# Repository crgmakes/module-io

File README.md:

# I/O Module

All the source files for the I/O module hardware.

# Software 

You will need [KiCad](https://kicad.org) to view and edit this design. Click [here](https://www.kicad.org/download/) to download.

You will also need all the associated libraries and models to drive the design if you want to make changes or view the 3D rendering:

https://github.com/crgmakes/kicad-library.git

Kicad MUST be configured properly to use all the files in this repo. Once you have Kicad installed, under Preferences->Configure Paths..., make the following entries:

1. KICAD_USER_DIR -> set to the root location of where you placed the above repository.
2. KICAD_USER_LIBRARY = ${KICAD_USER_DIR}/Library
3. KICAD_USER_MODEL_DIR = ${KICAD_USER_LIBRARY}/models
4. KICAD_USER_TEMPLATE_DIR = ${KICAD_USER_LIBRARY}/templates	

Kicad will operate mostly normally if these are not set properly. You will notice an issue when you view the PCB in 3D mode.

***NOTE***: after makeing a release build in git, if your rendered 3D images are missing components, ensure the path to EVERY component model is set to ${KICAD_USER_MODEL_DIR}/<model name>.

Kicad sometimes replaces the variable with an expansion and that FAILS during the build process because the expanded variable is local and does not match the build environment.

---

THE DESIGN IS PROVIDED "AS IS" AND THE AUTHOR DISCLAIMS ALL WARRANTIES WITH REGARD TO THIS DESIGN INCLUDING ALL IMPLIED WARRANTIES OF MERCHANTABILITY AND FITNESS. IN NO EVENT SHALL THE AUTHOR BE LIABLE FOR ANY SPECIAL, DIRECT, INDIRECT, OR CONSEQUENTIAL DAMAGES OR ANY DAMAGES WHATSOEVER RESULTING FROM LOSS OF USE, DATA OR PROFITS, WHETHER IN AN ACTION OF CONTRACT, NEGLIGENCE OR OTHER TORTIOUS ACTION, ARISING OUT OF OR IN CONNECTION WITH THE USE OR PERFORMANCE OF THIS DESIGN.

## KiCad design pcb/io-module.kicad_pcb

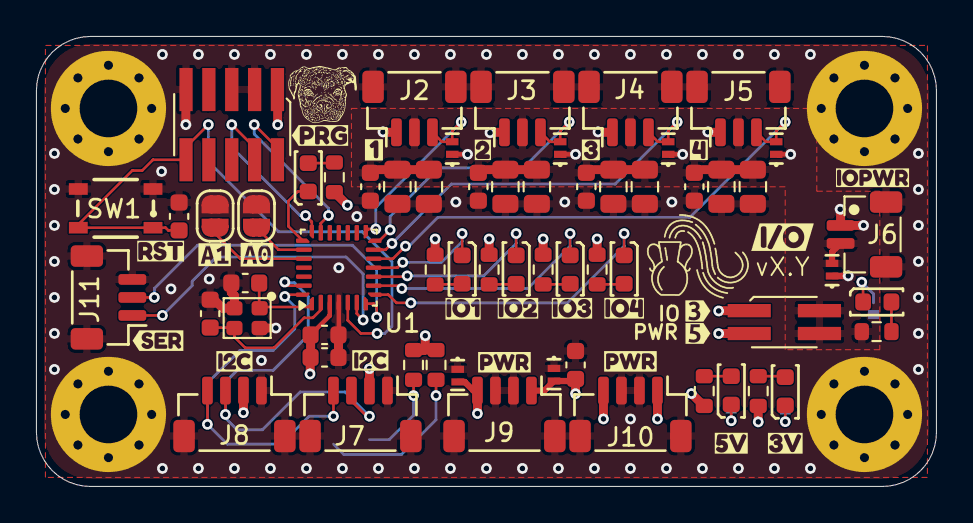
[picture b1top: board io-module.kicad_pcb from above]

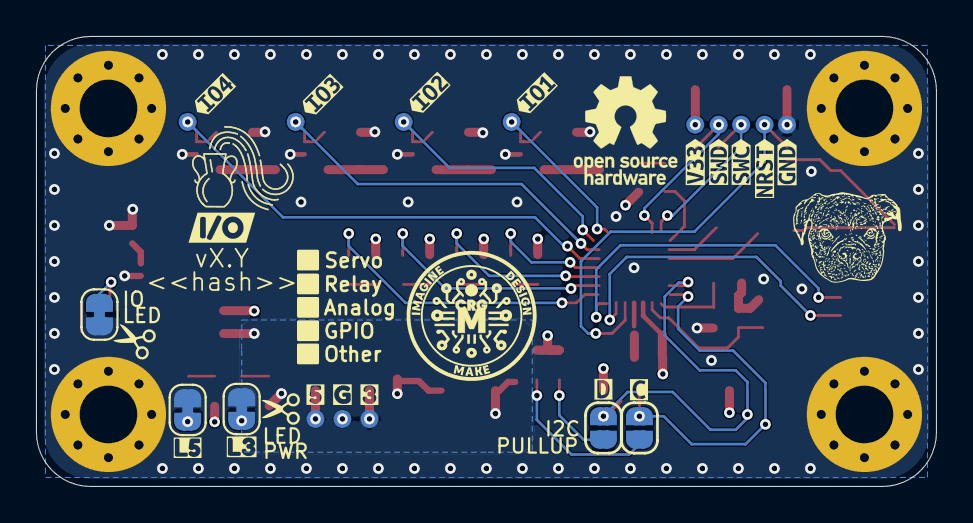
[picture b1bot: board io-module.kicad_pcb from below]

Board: 4 copper layers, 50.0 x 25.0 mm, 127 parts (38 on the bottom side), 37 nets.

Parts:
C1, C2: 4.7pF; C_0603_1608Metric
C3: 4.7uF; C_0603_1608Metric
C4, C5, C9, C12, C15, C18: 0.1uF; C_0603_1608Metric
C7, C8, C10, C11, C13, C14, C16, C17: 47uF; C_0805_2012Metric
C19: 10uF; C_0603_1608Metric
D1, D2, D3, D4, D12, D13, D14, D15: Blue; LED_0603_1608Metric
D5, D10: PESD5V5C1BL; DFN1006-2
D6, D7, D8, D9, D11: PESD3V3S1BL; DFN1006-2
H1, H2, H3, H4: MountingHole; MountingHole_3.2mm_M3_Pad_Via
J1: SWD Header; PinHeader_2x05_P1.27mm_Vertical_SMD
J2, J3, J4, J5, J11: JST_SH_BM03B-SRSS-TB_1x03-1MP_P1.00mm_Vertical
J6: JST_SH_BM02B-SRSS-TB_1x02-1MP_P1.00mm_Vertical
J7, J8, J9, J10: JST_SH_BM04B-SRSS-TB_1x04-1MP_P1.00mm_Vertical
J12: Conn_02x02_Odd_Even; PinHeader_2x02_P1.27mm_Vertical_SMD
JP1, JP2, JP3, JP4: SolderJumper_2_Open; SolderJumper-2_P1.3mm_Open_RoundedPad1.0x1.5mm
JP6, JP7, JP8: SolderJumper_2_Bridged; SolderJumper-2_P1.3mm_Bridged_RoundedPad1.0x1.5mm
LOGO1, LOGO2: Aquarius Logo 5mm
LOGO3: CRGM Logo 7mm
LOGO4: Logo_Open_Hardware_Small; OSHW-Logo_5.7x6mm_SilkScreen
LOGO5: Roxy 3.5mm
LOGO6: Roxy 6.5mm
R1, R2, R7, R9: 4.7K; R_0603_1608Metric
R3, R4, R5, R6, R8, R10: 1K; R_0603_1608Metric
SW1: SKRPABE010; SMD-4P-4.2x3.2mm
TP1, TP2, TP3, TP9, TP10, TP17, TP18, TP19: TestPoint_Pad_D1.0mm
TP11: SERVO1; TestPoint_Pad_D1.0mm
TP12: SERVO2; TestPoint_Pad_D1.0mm
TP13: SERVO3; TestPoint_Pad_D1.0mm
TP14: SERVO4; TestPoint_Pad_D1.0mm
U1: STM32C051G8Ux; QFN-28_4x4mm_P0.5mm
Y1: ECS-480-10-37B2-RWN-TR; Crystal_SMD_2016-4Pin_2.0x1.6mm
kibuzzard-6A2A39A2: G***; kibuzzard-6A2A39A2
kibuzzard-6A2A39A9: G***; kibuzzard-6A2A39A9
kibuzzard-6A2A39B0: G***; kibuzzard-6A2A39B0
kibuzzard-6A2B43CF: G***; kibuzzard-6A2B43CF
kibuzzard-6A2D8D87: G***; kibuzzard-6A2D8D87
kibuzzard-6A2EE621: G***; kibuzzard-6A2EE621
kibuzzard-6A2EE631: G***; kibuzzard-6A2EE631
kibuzzard-6A540D5A: G***; kibuzzard-6A540D5A
kibuzzard-6A540D7E: G***; kibuzzard-6A540D7E
kibuzzard-6A540D73: G***; kibuzzard-6A540D73
kibuzzard-6A540D79: G***; kibuzzard-6A540D79
kibuzzard-6A540D85: G***; kibuzzard-6A540D85
kibuzzard-6A972EAD: G***; kibuzzard-6A972EAD
kibuzzard-6A972EB4: G***; kibuzzard-6A972EB4
kibuzzard-6A7271F3: G***; kibuzzard-6A7271F3
kibuzzard-6A72720D: G***; kibuzzard-6A72720D
kibuzzard-6A72721E: G***; kibuzzard-6A72721E
kibuzzard-6A72852B: G***; kibuzzard-6A72852B
kibuzzard-6A72853D: G***; kibuzzard-6A72853D
kibuzzard-6A98747D: G***; kibuzzard-6A98747D
kibuzzard-6A727216: G***; kibuzzard-6A727216
kibuzzard-6A727224: G***; kibuzzard-6A727224
kibuzzard-6A727235: G***; kibuzzard-6A727235
kibuzzard-6A727258: G***; kibuzzard-6A727258
kibuzzard-6A728531: G***; kibuzzard-6A728531
kibuzzard-6A728536: G***; kibuzzard-6A728536
kibuzzard-690A7DF7: G***; kibuzzard-690A7DF7
kibuzzard-690A7E03: G***; kibuzzard-690A7E03
kibuzzard-690AC3C6: G***; kibuzzard-690AC3C6
kibuzzard-690AC3CC: G***; kibuzzard-690AC3CC
kibuzzard-690AC3D2: G***; kibuzzard-690AC3D2
kibuzzard-690D5FD9: G***; kibuzzard-690D5FD9
kibuzzard-690D5FF2: G***; kibuzzard-690D5FF2
kibuzzard-6954A310: G***; kibuzzard-6954A310
kibuzzard-6954A315: G***; kibuzzard-6954A315
kibuzzard-691760A0: G***; kibuzzard-691760A0
kibuzzard-6917603D: G***; kibuzzard-6917603D
kibuzzard-6917608E: G***; kibuzzard-6917608E
kibuzzard-69176003: G***; kibuzzard-69176003
kibuzzard-69176035: G***; kibuzzard-69176035

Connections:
+3.3V: C3.1, C4.1, C19.1, D11.2 (K2), J1.1 (VTref), J7.2, J8.2, J9.1 (V3), J10.1 (V3), J12.1, R1.2, R2.2, R3.1, R4.1, R5.1, R6.1, R8.1, R10.1, TP2.1 (1_1), TP18.1 (1_1), U1.3 (VDD)
+5V: D10.2 (K2), J9.4 (V5), J10.4 (V5), J12.3, R7.1, TP17.1 (1_1)
/MCU/A0: JP3.2 (B), U1.23 (PB3)
/MCU/A1: JP4.2 (B), U1.24 (PB4)
/MCU/LED1: D1.1 (K), U1.11 (PA5)
/MCU/LED2: D2.1 (K), U1.10 (PA4)
/MCU/LED3: D3.1 (K), U1.9 (PA3)
/MCU/LED4: D4.1 (K), U1.8 (PA2)
/MCU/STATUS: D15.1 (K), U1.22 (PA15)
/Power/V3.3LED: D13.2 (A), R8.2
/Power/V5LED: D12.2 (A), R7.2
/Power/VIOLED: D14.2 (A), R9.2
GND: C1.1, C2.1, C3.2, C4.2, C5.2, C7.2, C8.2, C9.2, C10.2, C11.2, C12.2, C13.2, C14.2, C15.2, C16.2, C17.2, C18.2, C19.2, D5.1 (K1), D6.1 (K1), D7.1 (K1), D8.1 (K1), D9.1 (K1), D10.1 (K1), D11.1 (K1), H1.1 (1_1), H2.1 (1_1), H3.1 (1_1), H4.1 (1_1), J1.3 (GND), J1.5 (GND), J1.9 (GNDDetect), J2.0 (MP), J2.1, J2.4 (MP), J3.0 (MP), J3.1, J3.4 (MP), J4.0 (MP), J4.1, J4.4 (MP), J5.0 (MP), J5.1, J5.4 (MP), J6.0 (MP), J6.1, J6.3 (MP), J7.0 (MP), J7.1, J7.5 (MP), J8.0 (MP), J8.1, J8.5 (MP), J9.0 (MP), J9.2 (GND), J9.3 (GND), J9.5 (MP), J10.0 (MP), J10.2 (GND), J10.3 (GND), J10.5 (MP), J11.0 (MP), J11.3, J11.4 (MP), JP3.1 (A), JP4.1 (A), JP6.1 (A), JP7.1 (A), JP8.1 (A), SW1.3, SW1.4, TP3.1 (1_1), TP19.1 (1_1), U1.4 (VSS), Y1.2 (G), Y1.4 (G)
IO1: D6.2 (K2), J2.3, TP11.1 (1_1), U1.15 (PB1)
IO2: D7.2 (K2), J3.3, TP12.1 (1_1), U1.14 (PB0)
IO3: D8.2 (K2), J4.3, TP13.1 (1_1), U1.13 (PA7)
IO4: D9.2 (K2), J5.3, TP14.1 (1_1), U1.12 (PA6)
NRST: C5.1, J1.10 (~RESET), SW1.1, SW1.2, TP1.1 (1_1), U1.5 (PF2-NRST)
unnamed: D1.2 (A), R3.2
unnamed: D2.2 (A), R4.2
unnamed: D3.2 (A), R5.2
unnamed: D4.2 (A), R6.2
unnamed: D12.1 (K), JP6.2 (B)
unnamed: D13.1 (K), JP7.2 (B)
unnamed: D14.1 (K), JP8.2 (B)
unnamed: D15.2 (A), R10.2
unnamed: JP1.2 (B), R1.1
unnamed: JP2.2 (B), R2.1
unnamed: C2.2, U1.1 (PC14/OSCXIN), Y1.1
unnamed: C1.2, U1.2 (PC15/OSCXO), Y1.3
RXD: J11.2, U1.7 (PA1)
SCL: J7.4, J8.4, JP1.1 (A), U1.28 (PB8)
SDA: J7.3, J8.3, JP2.1 (A), U1.27 (PB7)
SWCLK: J1.4 (SWDCLK/TCK), TP9.1 (1_1), U1.21 (PA14-BOOT0)
SWDIO: J1.2 (SWDIO/TMS), TP10.1 (1_1), U1.20 (PA13)
TXD: J11.1, U1.6 (PA0)
VIO: C7.1, C8.1, C9.1, C10.1, C11.1, C12.1, C13.1, C14.1, C15.1, C16.1, C17.1, C18.1, D5.2 (K2), J2.2, J3.2, J4.2, J5.2, J6.2, J12.2, J12.4, R9.1
